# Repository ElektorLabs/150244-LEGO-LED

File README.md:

LEGO LED
========

This is Elektor project 150244:

A small PCB compatible with LEGO bricks that can hold an LED.

More info:

www.elektor-magazine.com/150244

www.elektor.com

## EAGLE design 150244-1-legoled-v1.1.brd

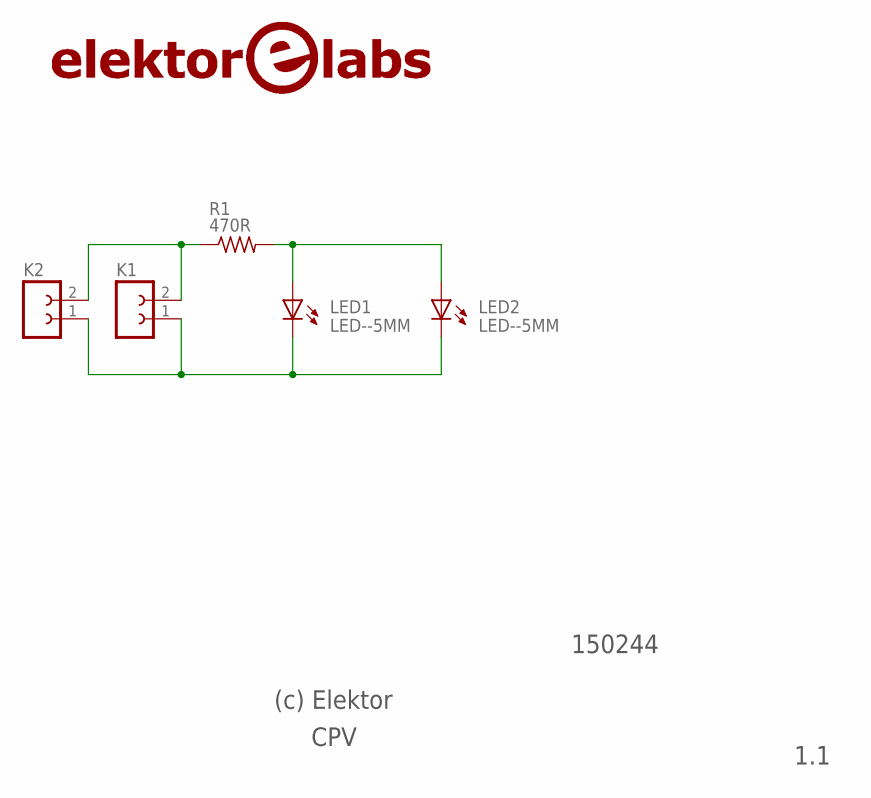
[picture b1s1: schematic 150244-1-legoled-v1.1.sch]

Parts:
K1, K2: K-HEADER-FEMALE-1X2-H; EPP-SIL-F-2-WAY-90DEG
LED1, LED2: LED--5MM; EPP-LED-5MM
LOGO1: LOGO-ELEKTOR-LABS-18MM-V2; EPP-LOGO-ELEKTOR-LABS-V2-18MM
R1: 470R; R0805

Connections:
unnamed: K1.2, K2.2, R1.1
unnamed: LED1.A, LED2.A, R1.2
unnamed: K1.1, K2.1, LED1.C, LED2.C

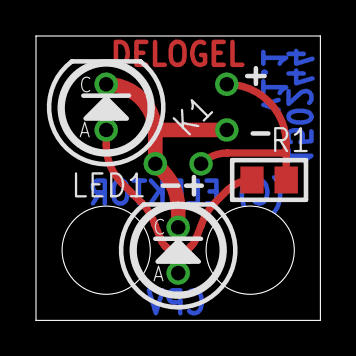
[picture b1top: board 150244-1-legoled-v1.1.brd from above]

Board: 2 copper layers, 15.8 x 15.8 mm, 6 parts (1 on the bottom side), 3 nets.

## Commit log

2015-06-11 :confetti_ball: Added .gitattributes & .gitignore files
2015-06-11 v1.0

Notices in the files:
150244-1-legoled-v1.1.brd:
COPYRIGHT: (C) ELEKTOR
